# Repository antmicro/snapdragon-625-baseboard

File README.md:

# Antmicro's open source SC606T (Snapdragon 625) Baseboard

Copyright (c) 2022-2024 [Antmicro](https://www.antmicro.com)

## Overview

This repository contains open hardware design files for an experimental development board for Quectel [SC606T Smart Module](https://www.quectel.com/product/lte-sc606t-smart-module-series) featuring Qualcomm [Snapdragon 625 Mobile Platform](https://www.qualcomm.com/products/application/smartphones/snapdragon-6-series-mobile-platforms/snapdragon-625-mobile-platform).
This development board break-routes the relevant I/O interfaces from the smart module keeping a small mechanical outline. 
The design files were prepared in KiCad 7.

## Repository structure

The main repository directory contains KiCad PCB project files, a LICENSE and README.
The remaining files are stored in the following directories:

* `img` - contains graphics for this README
* `doc` - contains schematics in PDF format
* `assets` - contains visual assets for showcasing this design on [Open Hardware Portal](https://openhardware.antmicro.com).

## Key Features

* Quectel SC606T Smart Module with Qualcomm Snapdragon 625
* Built-in Dual-Band WiFi and Bluetooth
* Built-in Cat 6 LTE modem with multi-constellation GNSS receiver
* HDMI output implemented with on-board DSI-HDMI bridge
* DSI interface exposed on Flexible Flat Cable (FFC) connector
* USB 3.0 (Type-C) connector supporting host/otg mode
* 2x 4-lane MIPI CSI-2 camera interface

The board supports multiple power supply scenarios including:

* USB-C PD (Power Delivery)
* External PSU or battery

The on-board camera connector is electrically compatible with several video accessories created by Antmicro such as:
 
* [OV9281 Dual Camera Board](https://github.com/antmicro/ov9281-camera-board)
* [SDI-MIPI bridge](https://github.com/antmicro/sdi-mipi-bridge)
* [HDMI-MIPI bridge](https://github.com/antmicro/hdmi-mipi-bridge)

## License

[Apache-2.0](LICENSE)

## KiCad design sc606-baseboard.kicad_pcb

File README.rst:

SC606T Baseboard
================

This repository includes an experimental hardware design of a baseboard using Quectel's SC606T System on Modue (SoM).

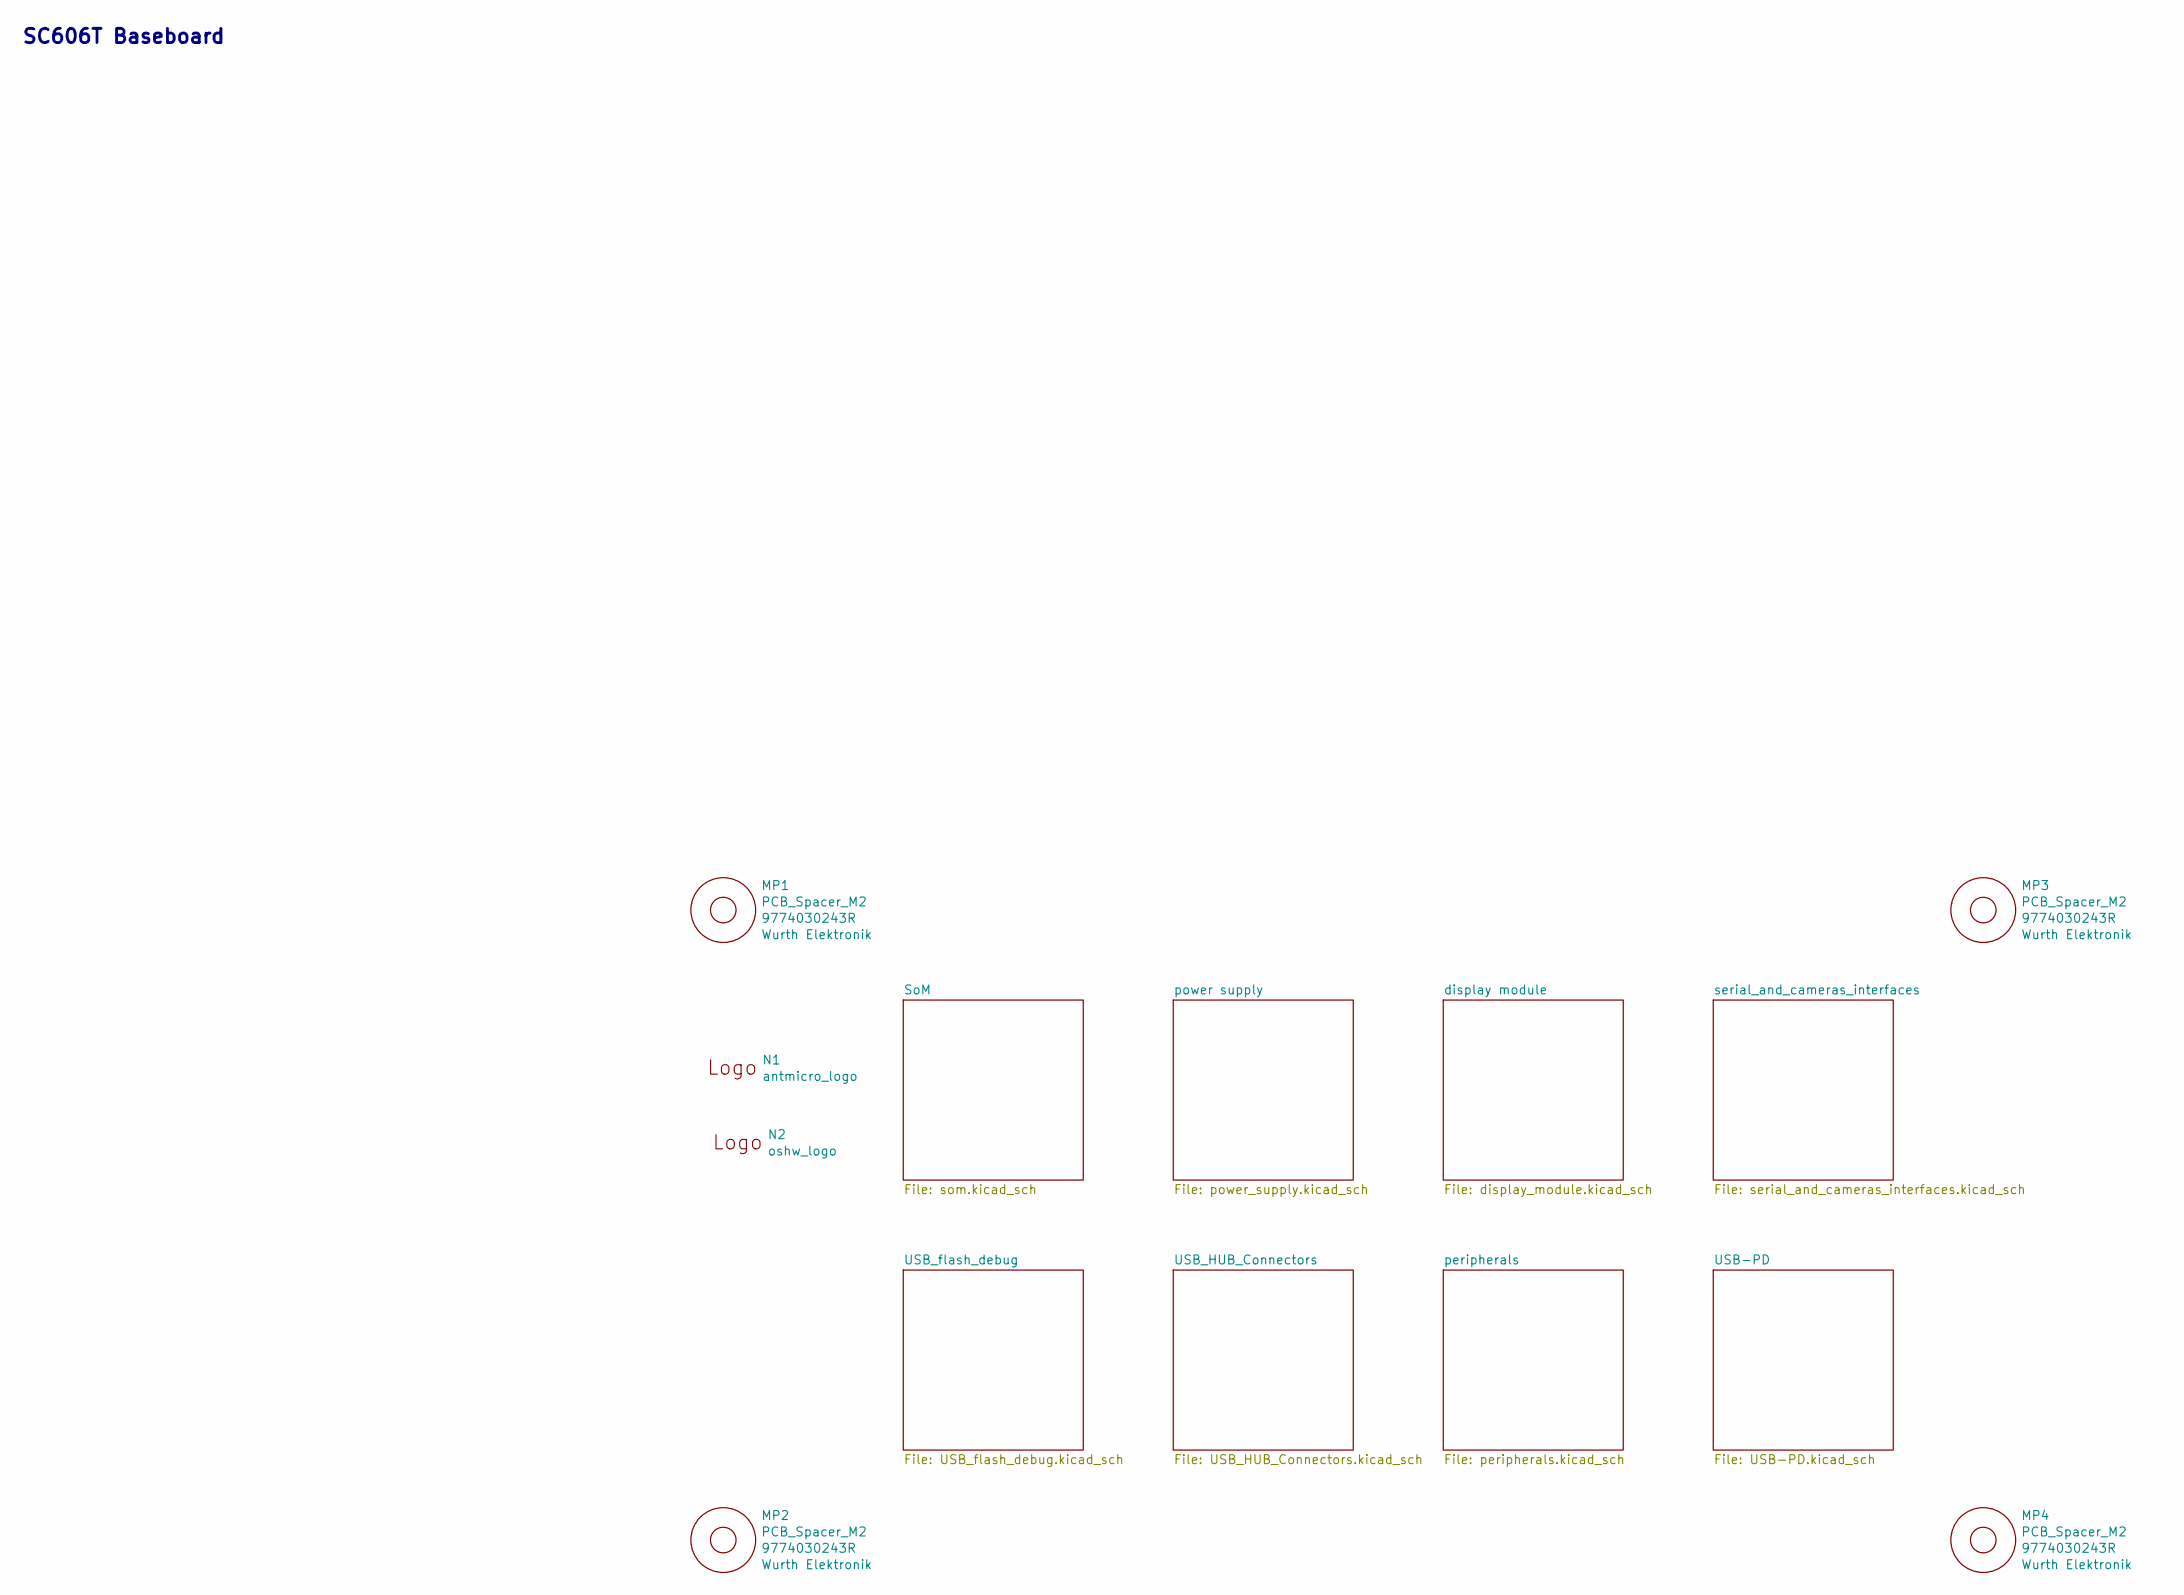
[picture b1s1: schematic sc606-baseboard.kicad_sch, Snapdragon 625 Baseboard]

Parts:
MP1, MP2, MP3, MP4: PCB_Spacer_M2; 9774030243R; MPN 9774030243R
N1: antmicro_logo; antmicro-logo_scaled_12mm
N2: oshw_logo; oshw-logo

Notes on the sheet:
SC606T Baseboard

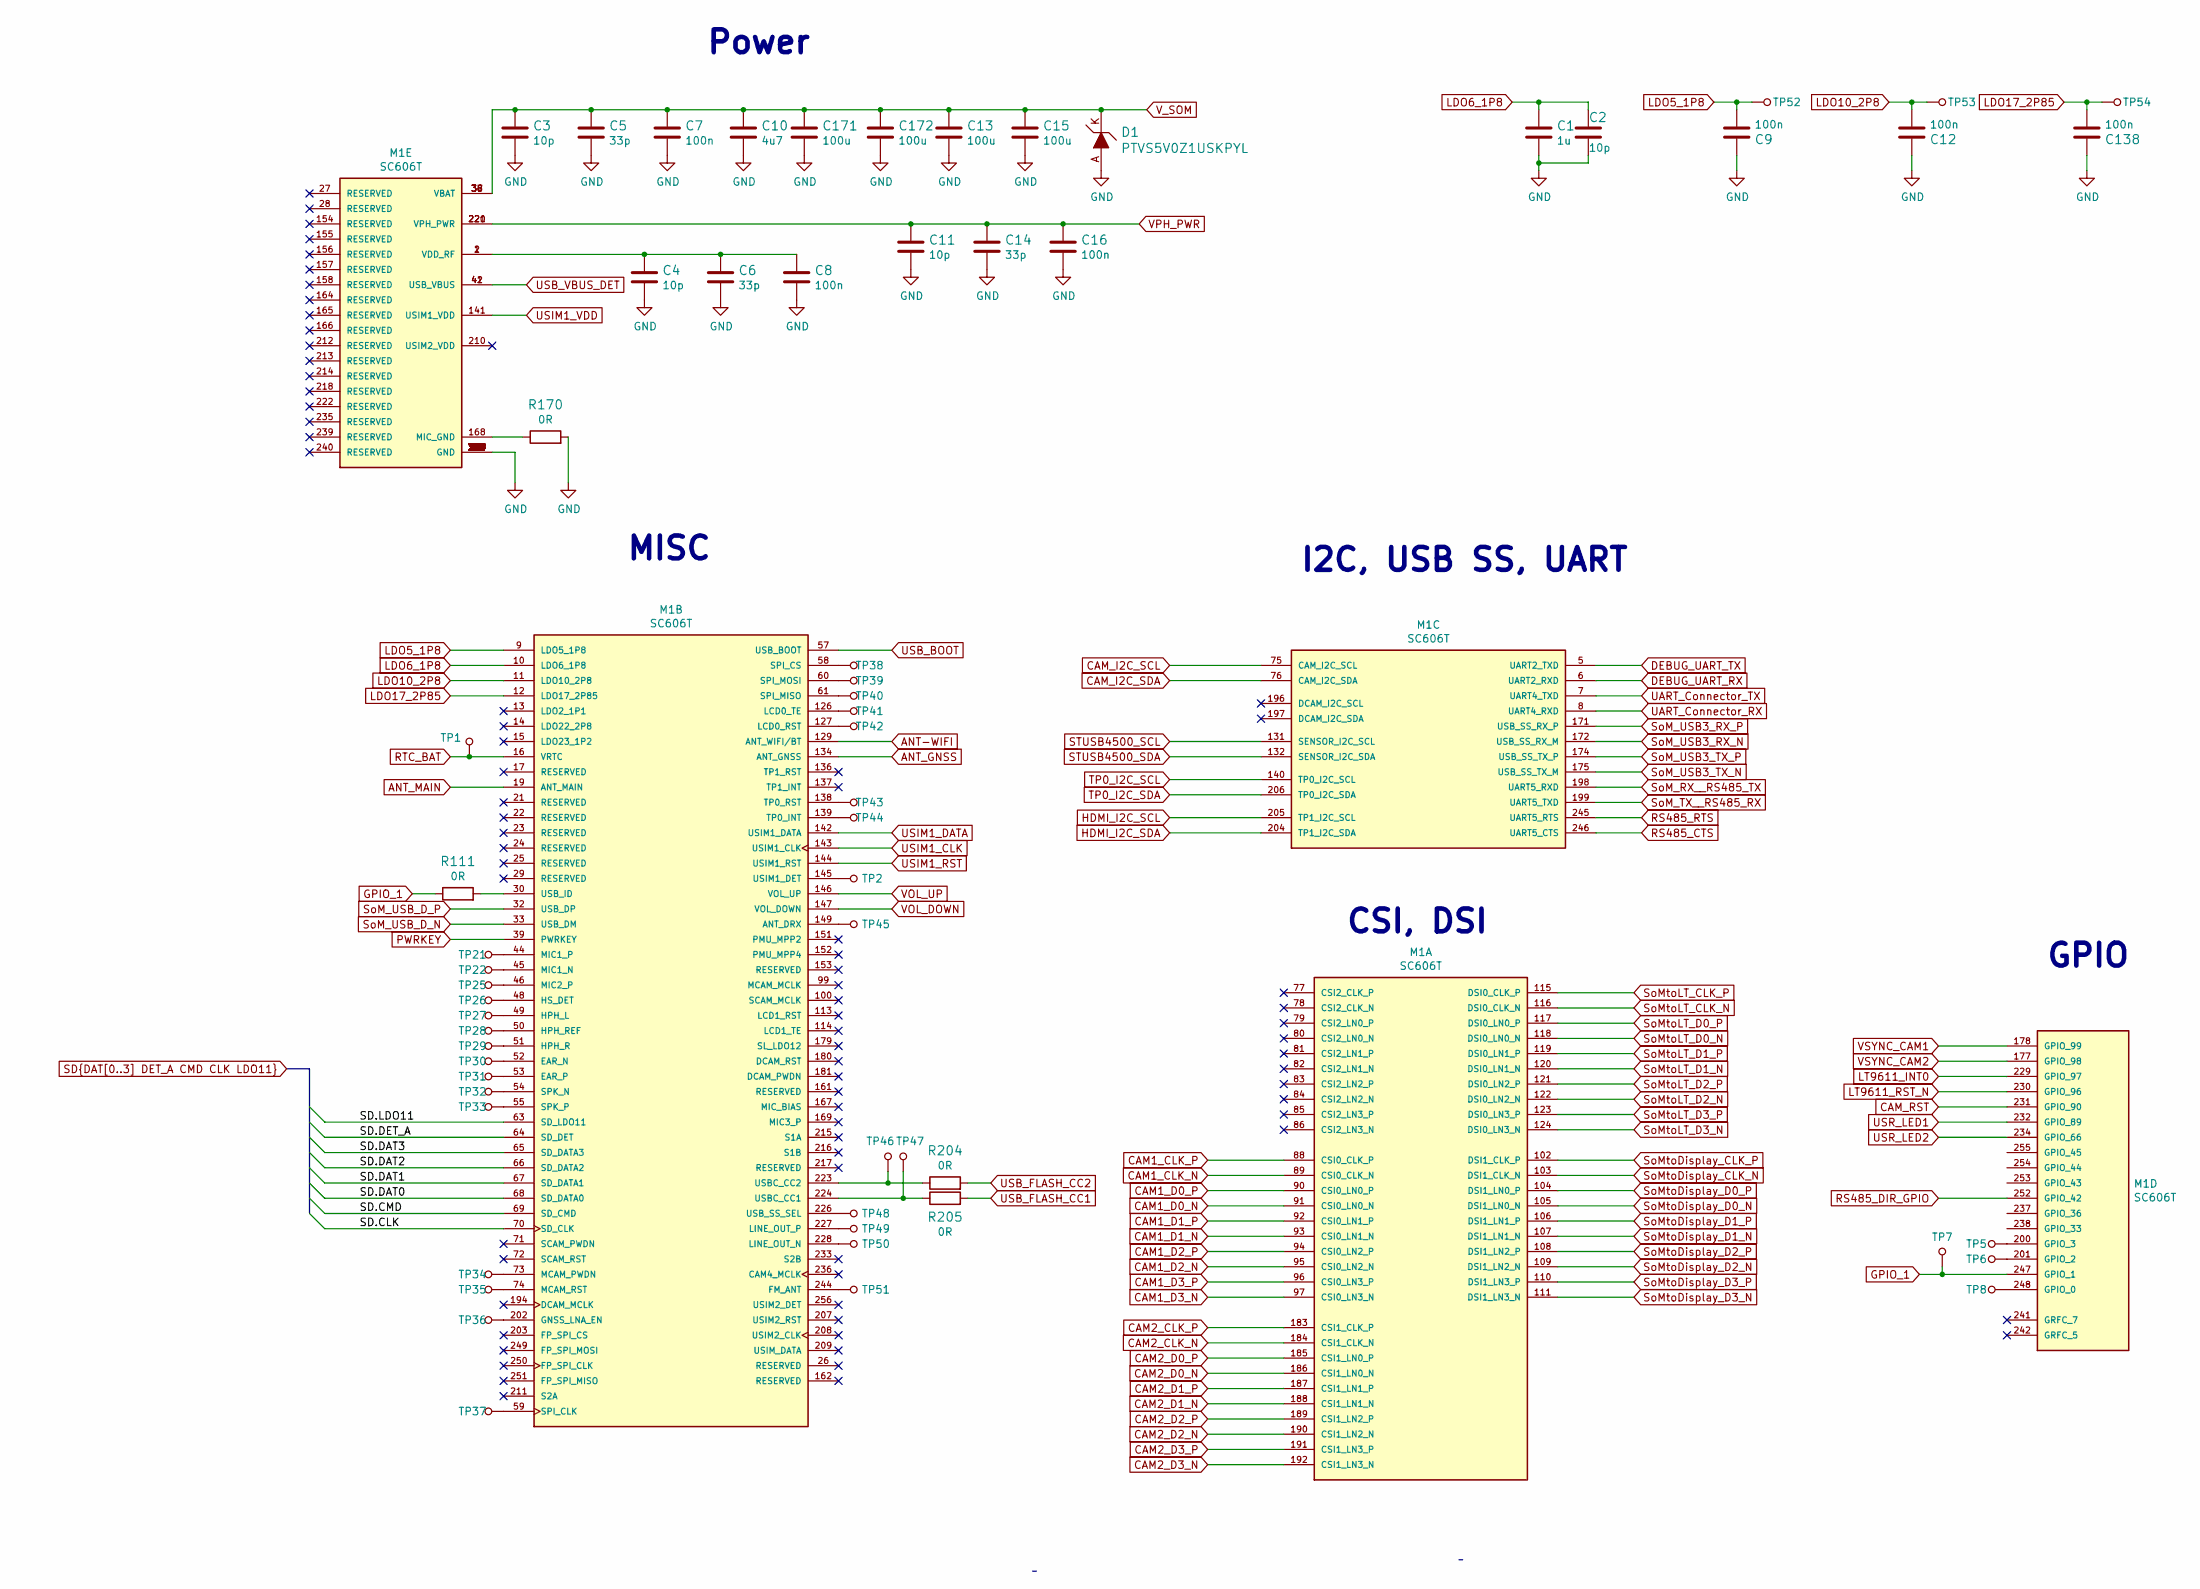
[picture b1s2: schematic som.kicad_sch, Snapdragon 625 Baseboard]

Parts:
C1: C_1u_0402; 0402-cap; MPN C1005X6S1A105K050BC
C2, C3, C4, C11: C_10p_0402; 0402-cap; MPN MC0402N100D500CT
C5, C6, C14: C_33p_0402; 0402-cap; MPN MC0402N330J500CT
C7, C8, C9, C12, C16, C138: C_100n_0402; 0402-cap; MPN 0402X104K6R3CT
C10: C_4u7_0402; 0402-cap; MPN GRM155R61A475MEAAD
C13, C15, C171, C172: C_100u_1206; 1206-cap; MPN TMCMA0J107MTRF
D1: PTVS5V0Z1USKPYL; SOD-964; MPN PTVS5V0Z1USKPYL
M1: SC606T; QUECTEL_SC606T; MPN SC606T-xx
R111, R170, R204, R205: R_0R_0402; 0402-res; MPN ERJ2GE0R00X
TP1, TP2, TP5, TP6, TP7, TP8, TP21, TP22, TP25, TP26, TP27, TP28, TP29, TP30, TP31, TP32, TP33, TP34, TP35, TP36, TP37, TP38, TP39, TP40, TP41, TP42, TP43, TP44, TP45, TP46, TP47, TP48, TP49, TP50, TP51, TP52, TP53, TP54: TP_SMD_1_5MM; TP-R-1.5

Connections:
ANT-WIFI: M1.129 (ANT_WIFI/BT); also elsewhere on the board
ANT_GNSS: M1.134 (ANT_GNSS); also elsewhere on the board
ANT_MAIN: M1.19 (ANT_MAIN); also elsewhere on the board
CAM1_CLK_N: M1.89 (CSI0_CLK_N); also elsewhere on the board
CAM1_CLK_P: M1.88 (CSI0_CLK_P); also elsewhere on the board
CAM1_D0_N: M1.91 (CSI0_LN0_N); also elsewhere on the board
CAM1_D0_P: M1.90 (CSI0_LN0_P); also elsewhere on the board
CAM1_D1_N: M1.93 (CSI0_LN1_N); also elsewhere on the board
CAM1_D1_P: M1.92 (CSI0_LN1_P); also elsewhere on the board
CAM1_D2_N: M1.95 (CSI0_LN2_N); also elsewhere on the board
CAM1_D2_P: M1.94 (CSI0_LN2_P); also elsewhere on the board
CAM1_D3_N: M1.97 (CSI0_LN3_N); also elsewhere on the board
CAM1_D3_P: M1.96 (CSI0_LN3_P); also elsewhere on the board
CAM2_CLK_N: M1.184 (CSI1_CLK_N); also elsewhere on the board
CAM2_CLK_P: M1.183 (CSI1_CLK_P); also elsewhere on the board
CAM2_D0_N: M1.186 (CSI1_LN0_N); also elsewhere on the board
CAM2_D0_P: M1.185 (CSI1_LN0_P); also elsewhere on the board
CAM2_D1_N: M1.188 (CSI1_LN1_N); also elsewhere on the board
CAM2_D1_P: M1.187 (CSI1_LN1_P); also elsewhere on the board
CAM2_D2_N: M1.190 (CSI1_LN2_N); also elsewhere on the board
CAM2_D2_P: M1.189 (CSI1_LN2_P); also elsewhere on the board
CAM2_D3_N: M1.192 (CSI1_LN3_N); also elsewhere on the board
CAM2_D3_P: M1.191 (CSI1_LN3_P); also elsewhere on the board
CAM_I2C_SCL: M1.75 (CAM_I2C_SCL); also elsewhere on the board
CAM_I2C_SDA: M1.76 (CAM_I2C_SDA); also elsewhere on the board
CAM_RST: M1.231 (GPIO_90); also elsewhere on the board
DEBUG_UART_RX: M1.6 (UART2_RXD); also elsewhere on the board
DEBUG_UART_TX: M1.5 (UART2_TXD); also elsewhere on the board
GND: C1.2, C2.2, C3.2, C4.2, C5.2, C6.2, C7.2, C8.2, C9.1, C10.2, C11.2, C12.1, C13.2, C14.2, C15.2, C16.2, C138.1, C171.2, C172.2, D1.A, M1.3 (GND), M1.4 (GND), M1.18 (GND), M1.20 (GND), M1.31 (GND), M1.34 (GND), M1.35 (GND), M1.40 (GND), M1.43 (GND), M1.47 (GND), M1.56 (GND), M1.62 (GND), M1.87 (GND), M1.98 (GND), M1.101 (GND), M1.112 (GND), M1.125 (GND), M1.128 (GND), M1.130 (GND), M1.133 (GND), M1.135 (GND), M1.148 (GND), M1.150 (GND), M1.159 (GND), M1.160 (GND), M1.163 (GND), M1.170 (GND), M1.173 (GND), M1.176 (GND), M1.182 (GND), M1.193 (GND), M1.195 (GND), M1.219 (GND), M1.225 (GND), M1.243 (GND), M1.257 (GND), M1.258 (GND), M1.259 (GND), M1.260 (GND), M1.261 (GND), M1.262 (GND), M1.263 (GND), M1.264 (GND), M1.265 (GND), M1.266 (GND), M1.267 (GND), M1.268 (GND), M1.269 (GND), M1.270 (GND), M1.271 (GND), M1.272 (GND), M1.273 (GND), M1.274 (GND), M1.275 (GND), M1.276 (GND), M1.277 (GND), M1.278 (GND), M1.279 (GND), M1.280 (GND), M1.281 (GND), M1.282 (GND), M1.283 (GND), M1.284 (GND), M1.285 (GND), M1.286 (GND), M1.287 (GND), M1.288 (GND), M1.289 (GND), M1.290 (GND), M1.291 (GND), M1.292 (GND), M1.293 (GND), M1.294 (GND), M1.295 (GND), M1.296 (GND), M1.297 (GND), M1.298 (GND), M1.299 (GND), M1.300 (GND), M1.301 (GND), M1.302 (GND), M1.303 (GND), M1.304 (GND), M1.305 (GND), M1.306 (GND), M1.307 (GND), M1.308 (GND), M1.309 (GND), M1.310 (GND), M1.311 (GND), M1.312 (GND), M1.313 (GND), M1.314 (GND), M1.315 (GND), M1.316 (GND), M1.317 (GND), M1.318 (GND), M1.319 (GND), M1.320 (GND), M1.321 (GND), M1.322 (GND), M1.323 (GND), R170.2; also elsewhere on the board
GPIO_1: M1.247 (GPIO_1), R111.1, TP7.1; also elsewhere on the board
HDMI_I2C_SCL: M1.205 (TP1_I2C_SCL); also elsewhere on the board
HDMI_I2C_SDA: M1.204 (TP1_I2C_SDA); also elsewhere on the board
LDO5_1P8: C9.2, M1.9 (LDO5_1P8), TP52.1; also elsewhere on the board
LDO6_1P8: C1.1, C2.1, M1.10 (LDO6_1P8); also elsewhere on the board
LDO10_2P8: C12.2, M1.11 (LDO10_2P8), TP53.1
LDO17_2P85: C138.2, M1.12 (LDO17_2P85), TP54.1; also elsewhere on the board
LT9611_INT0: M1.229 (GPIO_97); also elsewhere on the board
LT9611_RST_N: M1.230 (GPIO_96); also elsewhere on the board
unnamed: C4.1, C6.1, C8.1, M1.1 (VDD_RF), M1.2 (VDD_RF)
unnamed: M1.30 (USB_ID), R111.2
unnamed: M1.44 (MIC1_P), TP21.1
unnamed: M1.45 (MIC1_N), TP22.1
unnamed: M1.46 (MIC2_P), TP25.1
unnamed: M1.48 (HS_DET), TP26.1
unnamed: M1.49 (HPH_L), TP27.1
unnamed: M1.50 (HPH_REF), TP28.1
unnamed: M1.51 (HPH_R), TP29.1
unnamed: M1.52 (EAR_N), TP30.1
unnamed: M1.53 (EAR_P), TP31.1
unnamed: M1.54 (SPK_N), TP32.1
unnamed: M1.55 (SPK_P), TP33.1
unnamed: M1.58 (SPI_CS), TP38.1
unnamed: M1.59 (SPI_CLK), TP37.1
unnamed: M1.60 (SPI_MOSI), TP39.1
unnamed: M1.61 (SPI_MISO), TP40.1
unnamed: M1.73 (MCAM_PWDN), TP34.1
unnamed: M1.74 (MCAM_RST), TP35.1
unnamed: M1.126 (LCD0_TE), TP41.1
unnamed: M1.127 (LCD0_RST), TP42.1
unnamed: M1.138 (TP0_RST), TP43.1
unnamed: M1.139 (TP0_INT), TP44.1
unnamed: M1.145 (USIM1_DET), TP2.1
unnamed: M1.149 (ANT_DRX), TP45.1
unnamed: M1.168 (MIC_GND), R170.1
unnamed: M1.200 (GPIO_3), TP5.1
unnamed: M1.201 (GPIO_2), TP6.1
unnamed: M1.202 (GNSS_LNA_EN), TP36.1
unnamed: M1.223 (USBC_CC2), R204.1, TP46.1
unnamed: M1.224 (USBC_CC1), R205.1, TP47.1
unnamed: M1.226 (USB_SS_SEL), TP48.1
unnamed: M1.227 (LINE_OUT_P), TP49.1
unnamed: M1.228 (LINE_OUT_N), TP50.1
unnamed: M1.244 (FM_ANT), TP51.1
unnamed: M1.248 (GPIO_0), TP8.1
PWRKEY: M1.39 (PWRKEY); also elsewhere on the board
RS485_CTS: M1.246 (UART5_CTS); also elsewhere on the board
RS485_DIR_GPIO: M1.252 (GPIO_42); also elsewhere on the board
RS485_RTS: M1.245 (UART5_RTS); also elsewhere on the board
RTC_BAT: M1.16 (VRTC), TP1.1; also elsewhere on the board
SD_DATA_0: M1.68 (SD_DATA0); also elsewhere on the board
SD_DATA_1: M1.67 (SD_DATA1); also elsewhere on the board
SD_DATA_2: M1.66 (SD_DATA2); also elsewhere on the board
SD_DATA_3: M1.65 (SD_DATA3); also elsewhere on the board
SD_DATA_4: M1.70 (SD_CLK); also elsewhere on the board
SD_DATA_5: M1.69 (SD_CMD); also elsewhere on the board
SD_DATA_6: M1.64 (SD_DET); also elsewhere on the board
STUSB4500_SCL: M1.131 (SENSOR_I2C_SCL); also elsewhere on the board
STUSB4500_SDA: M1.132 (SENSOR_I2C_SDA); also elsewhere on the board
SoM_RX__RS485_TX: M1.198 (UART5_RXD); also elsewhere on the board
SoM_TX__RS485_RX: M1.199 (UART5_TXD); also elsewhere on the board
SoM_USB3_RX_N: M1.172 (USB_SS_RX_M); also elsewhere on the board
SoM_USB3_RX_P: M1.171 (USB_SS_RX_P); also elsewhere on the board
SoM_USB3_TX_N: M1.175 (USB_SS_TX_M); also elsewhere on the board
SoM_USB3_TX_P: M1.174 (USB_SS_TX_P); also elsewhere on the board
SoM_USB_D_N: M1.33 (USB_DM); also elsewhere on the board
SoM_USB_D_P: M1.32 (USB_DP); also elsewhere on the board
SoMtoDisplay_CLK_N: M1.103 (DSI1_CLK_N); also elsewhere on the board
SoMtoDisplay_CLK_P: M1.102 (DSI1_CLK_P); also elsewhere on the board
SoMtoDisplay_D0_N: M1.105 (DSI1_LN0_N); also elsewhere on the board
SoMtoDisplay_D0_P: M1.104 (DSI1_LN0_P); also elsewhere on the board
SoMtoDisplay_D1_N: M1.107 (DSI1_LN1_N); also elsewhere on the board
SoMtoDisplay_D1_P: M1.106 (DSI1_LN1_P); also elsewhere on the board
SoMtoDisplay_D2_N: M1.109 (DSI1_LN2_N); also elsewhere on the board
SoMtoDisplay_D2_P: M1.108 (DSI1_LN2_P); also elsewhere on the board
SoMtoDisplay_D3_N: M1.111 (DSI1_LN3_N); also elsewhere on the board
SoMtoDisplay_D3_P: M1.110 (DSI1_LN3_P); also elsewhere on the board
SoMtoLT_CLK_N: M1.116 (DSI0_CLK_N); also elsewhere on the board
SoMtoLT_CLK_P: M1.115 (DSI0_CLK_P); also elsewhere on the board
SoMtoLT_D0_N: M1.118 (DSI0_LN0_N); also elsewhere on the board
SoMtoLT_D0_P: M1.117 (DSI0_LN0_P); also elsewhere on the board
SoMtoLT_D1_N: M1.120 (DSI0_LN1_N); also elsewhere on the board
SoMtoLT_D1_P: M1.119 (DSI0_LN1_P); also elsewhere on the board
SoMtoLT_D2_N: M1.122 (DSI0_LN2_N); also elsewhere on the board
SoMtoLT_D2_P: M1.121 (DSI0_LN2_P); also elsewhere on the board
SoMtoLT_D3_N: M1.124 (DSI0_LN3_N); also elsewhere on the board
SoMtoLT_D3_P: M1.123 (DSI0_LN3_P); also elsewhere on the board
TP0_I2C_SCL: M1.140 (TP0_I2C_SCL); also elsewhere on the board
TP0_I2C_SDA: M1.206 (TP0_I2C_SDA); also elsewhere on the board
UART_Connector_RX: M1.8 (UART4_RXD); also elsewhere on the board
UART_Connector_TX: M1.7 (UART4_TXD); also elsewhere on the board
USB_BOOT: M1.57 (USB_BOOT); also elsewhere on the board
USB_FLASH_CC1: R205.2; also elsewhere on the board
USB_FLASH_CC2: R204.2; also elsewhere on the board
USB_VBUS_DET: M1.41 (USB_VBUS), M1.42 (USB_VBUS); also elsewhere on the board
USIM1_CLK: M1.143 (USIM1_CLK); also elsewhere on the board
USIM1_DATA: M1.142 (USIM1_DATA); also elsewhere on the board
USIM1_RST: M1.144 (USIM1_RST); also elsewhere on the board
USIM1_VDD: M1.141 (USIM1_VDD); also elsewhere on the board
USR_LED1: M1.232 (GPIO_89); also elsewhere on the board
USR_LED2: M1.234 (GPIO_66); also elsewhere on the board
VOL_DOWN: M1.147 (VOL_DOWN); also elsewhere on the board
VOL_UP: M1.146 (VOL_UP); also elsewhere on the board
VPH_PWR: C11.1, C14.1, C16.1, M1.220 (VPH_PWR), M1.221 (VPH_PWR)
VSYNC_CAM1: M1.178 (GPIO_99); also elsewhere on the board
VSYNC_CAM2: M1.177 (GPIO_98); also elsewhere on the board
V_SOM: C3.1, C5.1, C7.1, C10.1, C13.1, C15.1, C171.1, C172.1, D1.K, M1.36 (VBAT), M1.37 (VBAT), M1.38 (VBAT); also elsewhere on the board

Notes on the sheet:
Power
CSI, DSI
MISC
I2C, USB SS, UART
GPIO

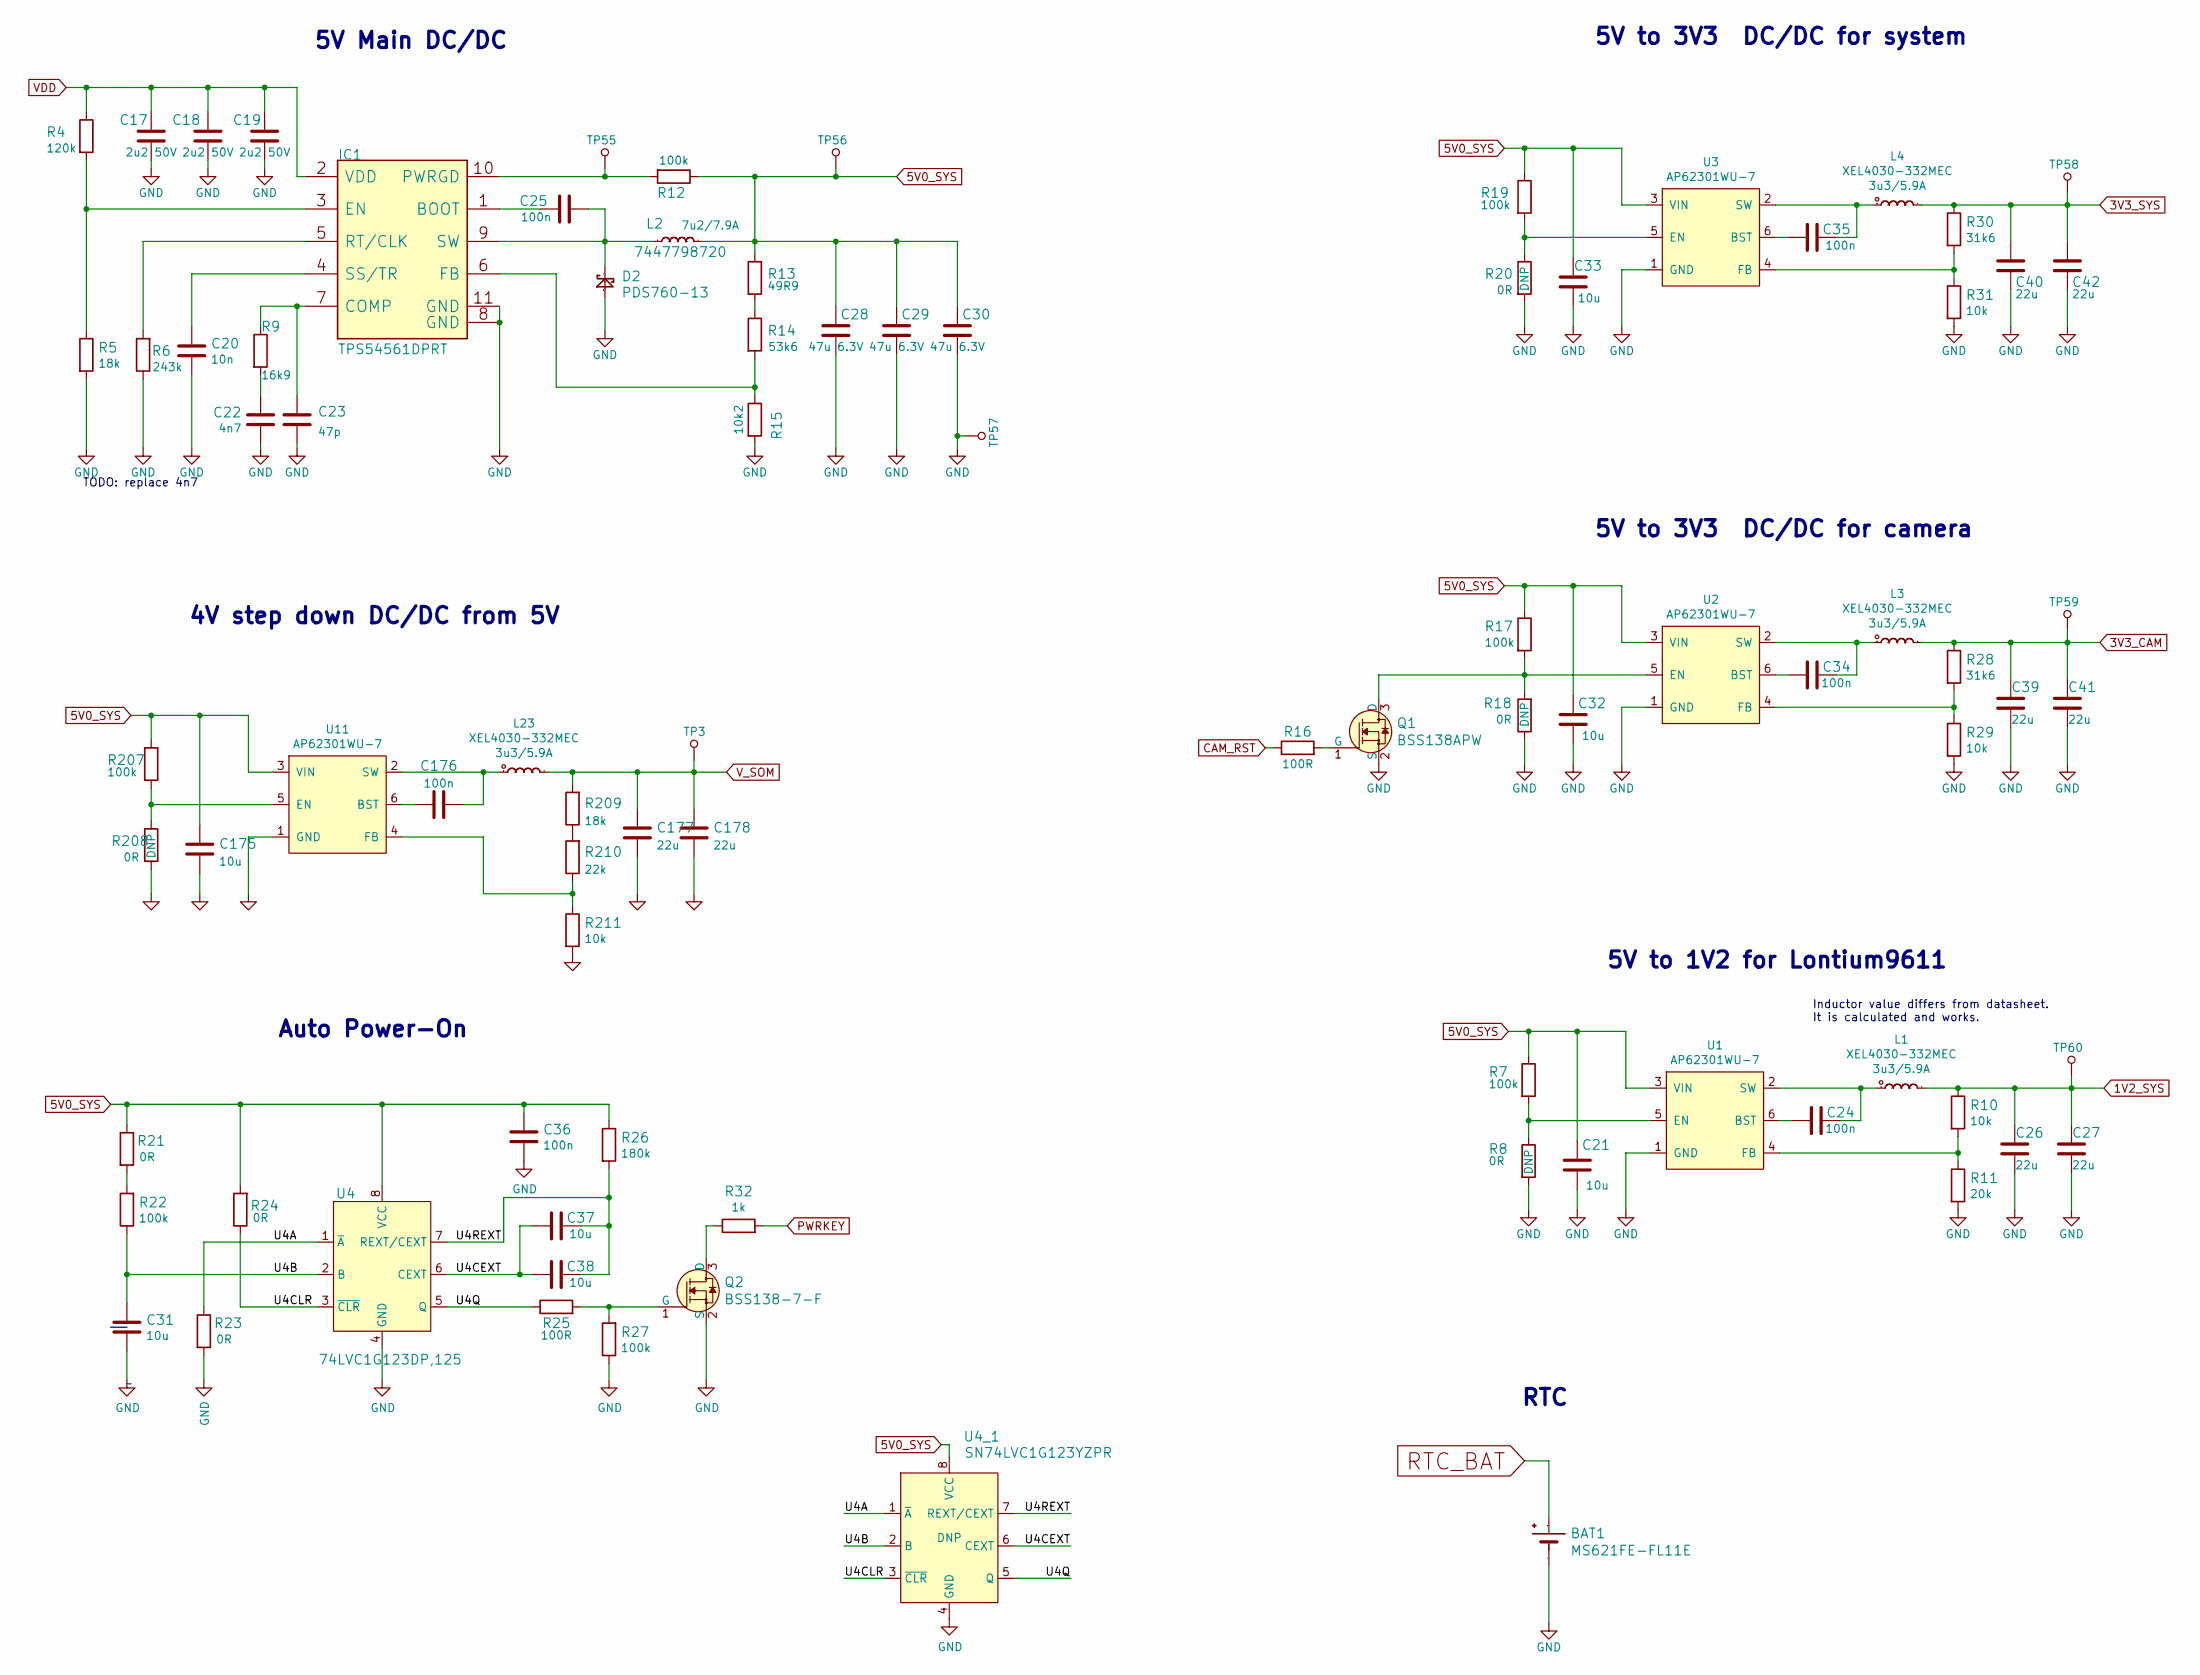
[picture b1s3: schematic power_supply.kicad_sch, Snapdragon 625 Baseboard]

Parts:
BAT1: MS621FE-FL11E; MPN MS621FE-FL11E
C17, C18, C19: C_2u2_0805_50V; 0805-cap; MPN C2012X5R1H225K125AB
C20: C_10n_0402; 0402-cap; MPN 04025G103ZAT2A
C21, C31, C32, C33, C37, C38, C175: C_10u_0402; 0402-cap; MPN CC0402MRX5R5BB106
C22: C_4n7_0402; 0402-cap; MPN CGA2B3X7S2A472K050BB
C23: C_47p_0402; 0402-cap; MPN C0402C470J5GACTU
C24, C34, C35, C36, C176: C_100n_0402; 0402-cap; MPN GRM155R61H104KE14D
C25: C_100n_0402; 0402-cap; MPN 0402X104K6R3CT
C26, C27, C39, C40, C41, C42: C_22u_0603; 0603-cap; MPN GRM188R60J226MEA0D
C28, C29, C30: C_47u_0603; 0603-cap; MPN GRM188R60J476ME15D
C177, C178: C_22u_0402; 0402-cap; MPN 04024W226MAT2A
D2: PDS760-13; MPN PDS760-13
IC1: TPS54561DPRT; WSON-10_4x4; MPN TPS54561DPRT
L1, L3, L4, L23: XEL4030-332MEC; Coilcraft-XEL4030; MPN XEL4030-332MEC
L2: 7447798720; WE_7447798720; MPN 7447798720
Q1: BSS138APW; SC70-3; MPN BSS138PW
Q2: BSS138-7-F; SOT-23-3; MPN BSS138-7-F
R4: R_120k_0402; 0402-res; MPN CRCW0402120KFKED
R5, R209: R_18k_0402; 0402-res; MPN MCWR04X1802FTL
R6: R_243k_0402; 0402-res; MPN MCMR04X2433FTL
R7, R12, R17, R19, R22, R27: R_100k_0402; 0402-res; MPN CRCW0402100KFKEDHP
R8, R18, R20, R21, R23, R24: R_0R_0402; 0402-res; MPN ERJ2GE0R00X
R9: R_16k9_0402; 0402-res; MPN ERA2AEB1692X
R10, R29, R31, R211: R_10k_0402; 0402-res; MPN CRCW040210K0FKEDHP
R11: R_20k_0402; 0402-res; MPN CRCW040220K0FKED
R13: R_49R9_0603; 0603-res; MPN CRCW060349R9FKEA
R14: R_53k6_0402; 0402-res; MPN CPF0402B53K6E1
R15: R_10k2_0402; 0402-res; MPN MCWR04X1022FTL
R16, R25: R_100R_0402; 0402-res; MPN CR0402-FX-1000GLF
R26: R_180k_0402; 0402-res; MPN CRCW0402180KJNED
R28, R30: R_31k6_0402; 0402-res; MPN CRCW040231K6FKEDC
R32: R_1k_0402; 0402-res; MPN CR0402-FX-1001GLF
R207: 0402-res; MPN CRCW0402100KFKEDHP
R208: 0402-res; MPN ERJ2GE0R00X
R210: R_22k_0402; 0402-res; MPN ERJ-2RKF2202X
TP3, TP55, TP56, TP57, TP58, TP59, TP60: TP_SMD_1_5MM; TP-R-1.5
U1, U2, U3, U11: AP62301WU-7; TSOT23-6; MPN AP62301WU-7
U4: 74LVC1G123DP,125; TSSOP-8_W3mm; MPN 74LVC1G123DP,125
U4_1: SN74LVC1G123YZPR; DSBGA-8_1.91x0.91mm; MPN SN74LVC1G123YZPR

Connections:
1V2_SYS: C26.1, C27.1, L1.2, R10.1, TP60.1; also elsewhere on the board
3V3_CAM: C39.1, C41.1, L3.2, R28.1, TP59.1; also elsewhere on the board
3V3_SYS: C40.1, C42.1, L4.2, R30.1, TP58.1; also elsewhere on the board
5V0_SYS: C21.1, C28.1, C29.1, C30.1, C32.1, C33.1, C36.2, C175.1, L2.2, R7.1, R12.1, R13.1, R17.1, R19.1, R21.1, R24.2, R26.1, R207.1, TP56.1, U1.3 (VIN), U2.3 (VIN), U3.3 (VIN), U4.8 (VCC), U4_1.8 (VCC), U11.3 (VIN); also elsewhere on the board
/power supply/U4A: R23.1, U4.1 (~A), U4_1.1 (~A)
/power supply/U4B: C31.1, R22.1, U4.2 (B), U4_1.2 (B)
/power supply/U4CEXT: C37.1, C38.1, U4.6 (CEXT), U4_1.6 (CEXT)
/power supply/U4CLR: R24.1, U4.3 (~CLR), U4_1.3 (~CLR)
/power supply/U4Q: R25.1, U4.5 (Q), U4_1.5 (Q)
/power supply/U4REXT: C37.2, C38.2, R26.2, U4.7 (REXT/CEXT), U4_1.7 (REXT/CEXT)
CAM_RST: R16.1; also elsewhere on the board
GND: BAT1.-, C17.2, C18.2, C19.2, C20.2, C21.2, C22.2, C23.2, C26.2, C27.2, C28.2, C29.2, C30.2, C31.2, C32.2, C33.2, C36.1, C39.2, C40.2, C41.2, C42.2, D2.A, IC1.8 (GND), IC1.11 (GND), Q1.2 (S), Q2.2 (S), R5.2, R6.1, R8.2, R11.2, R15.2, R18.1, R20.2, R23.2, R27.1, R29.2, R31.2, TP57.1, U1.1 (GND), U2.1 (GND), U3.1 (GND), U4.4 (GND), U4_1.4 (GND); also elsewhere on the board
unnamed: C20.1, IC1.4 (SS/TR)
unnamed: C22.1, R9.2
unnamed: C23.1, IC1.7 (COMP), R9.1
unnamed: C24.1, L1.1, U1.2 (SW)
unnamed: C24.2, U1.6 (BST)
unnamed: C25.1, IC1.1 (BOOT)
unnamed: C25.2, D2.C, IC1.9 (SW), L2.1
unnamed: C34.1, L3.1, U2.2 (SW)
unnamed: C34.2, U2.6 (BST)
unnamed: C35.1, L4.1, U3.2 (SW)
unnamed: C35.2, U3.6 (BST)
unnamed: C175.2, C177.2, C178.2, R208.2, R211.2, U11.1 (GND)
unnamed: C176.1, U11.6 (BST)
unnamed: C176.2, L23.1, U11.2 (SW)
unnamed: C177.1, C178.1, L23.2, R209.2, TP3.1
unnamed: IC1.3 (EN), R4.2, R5.1
unnamed: IC1.5 (RT/CLK), R6.2
unnamed: IC1.6 (FB), R14.2, R15.1
unnamed: IC1.10 (PWRGD), R12.2, TP55.1
unnamed: Q1.1 (G), R16.2
unnamed: Q1.3 (D), R17.2, R18.2, U2.5 (EN)
unnamed: Q2.1 (G), R25.2, R27.2
unnamed: Q2.3 (D), R32.1
unnamed: R7.2, R8.1, U1.5 (EN)
unnamed: R10.2, R11.1, U1.4 (FB)
unnamed: R13.2, R14.1
unnamed: R19.2, R20.1, U3.5 (EN)
unnamed: R21.2, R22.2
unnamed: R28.2, R29.1, U2.4 (FB)
unnamed: R30.2, R31.1, U3.4 (FB)
unnamed: R207.2, R208.1, U11.5 (EN)
unnamed: R209.1, R210.2
unnamed: R210.1, R211.1, U11.4 (FB)
PWRKEY: R32.2; also elsewhere on the board
RTC_BAT: BAT1.+; also elsewhere on the board
VDD: C17.1, C18.1, C19.1, IC1.2 (VDD), R4.1; also elsewhere on the board

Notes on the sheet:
5V to 3V3 DC/DC for camera
4V step down DC/DC from 5V
TODO: replace 4n7
5V Main DC/DC
Auto Power-On
RTC
5V to 1V2 for Lontium9611
Inductor value differs from datasheet. It is calculated and works.
5V to 3V3 DC/DC for system

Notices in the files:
parts and their libraries:
Copyright 2021 Accelerated Designs. All rights reserved.
